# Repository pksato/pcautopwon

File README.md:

Small circuit using 555 timer to poweron a computer without option on BIOS to manage poweron behavior, in case of power loss. 
  
Its have three connection:  
5VSB to power circuit direct from PSU.  
5V to detect if main PSU is on.  
Connection to main board power on switch header.  
          
The 555 is configured as astable oscillator, generating a sort ~1s low pulse every ~10s. This pulse lit the optocoupler led and close the transistor, simulating push of the power button. When power is on (presence of 5V), transistor Q1 saturate, pulling down reset pin of 555, and avoiding the optocoupler led to lit. On reset condition, output pin of 555 goes do low. The circuit are build on top of PCB (as SMT), to easy fix the board inside the PC case.
  
EagleCad files and PNG images.
  
OBS.:
The mainboard where this circuit is used don't have option on BIOS to manage power state when mains AC return. And power on when power switch is released. Also, have a delay after mains applied and able to press power button.

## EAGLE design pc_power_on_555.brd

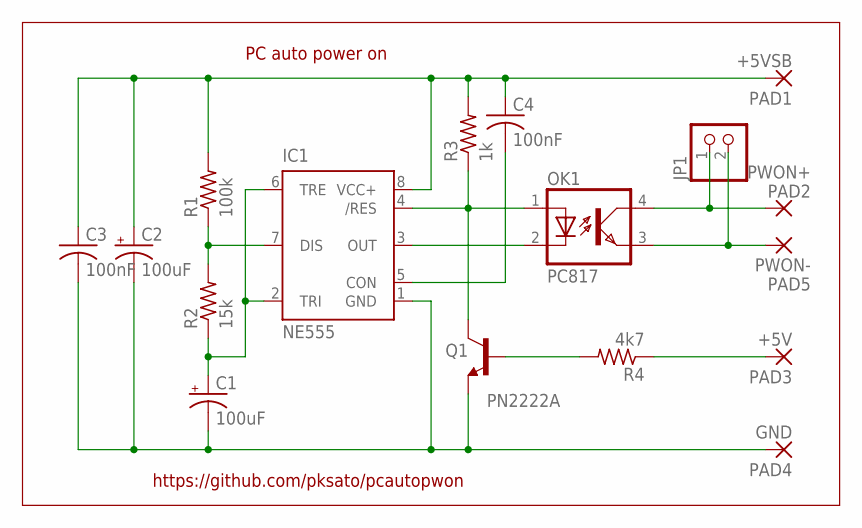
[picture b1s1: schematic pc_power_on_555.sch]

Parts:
C1, C2: 100uF; E2,5-7
C3, C4: 100nF; C025-030X050
IC1: NE555; DIL-08
JP1: PINHD-1X2; 1X02
OK1: PC817; DIL04
PAD1: +5VSB; 1,6/0,8
PAD2: PWON+; 1,6/0,8
PAD3: +5V; 1,6/0,8
PAD4: GND; 1,6/0,8
PAD5: PWON-; 1,6/0,8
Q1: PN2222A; TO92-EBC
R1: 100k; 0207/10
R2: 15k; 0207/10
R3: 1k; 0207/10
R4: 4k7; 0207/10

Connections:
unnamed: C1.+, IC1.2 (TRI), IC1.6 (TRE), R2.1
unnamed: IC1.7 (DIS), R1.1, R2.2
unnamed: IC1.3 (OUT), OK1.2 (C)
unnamed: C2.+, C3.1, C4.1, IC1.8 (VCC+), PAD1.1, R1.2, R3.2
unnamed: IC1.4 (/RES), OK1.1 (A), Q1.C, R3.1
unnamed: C1.-, C2.-, C3.2, IC1.1 (GND), PAD4.1, Q1.E
unnamed: JP1.2, OK1.3 (EMIT), PAD5.1
unnamed: JP1.1, OK1.4 (COL), PAD2.1
unnamed: Q1.B, R4.2
unnamed: PAD3.1, R4.1
unnamed: C4.2, IC1.5 (CON)

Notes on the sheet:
PC auto power on
https://github.com/pksato/pcautopwon

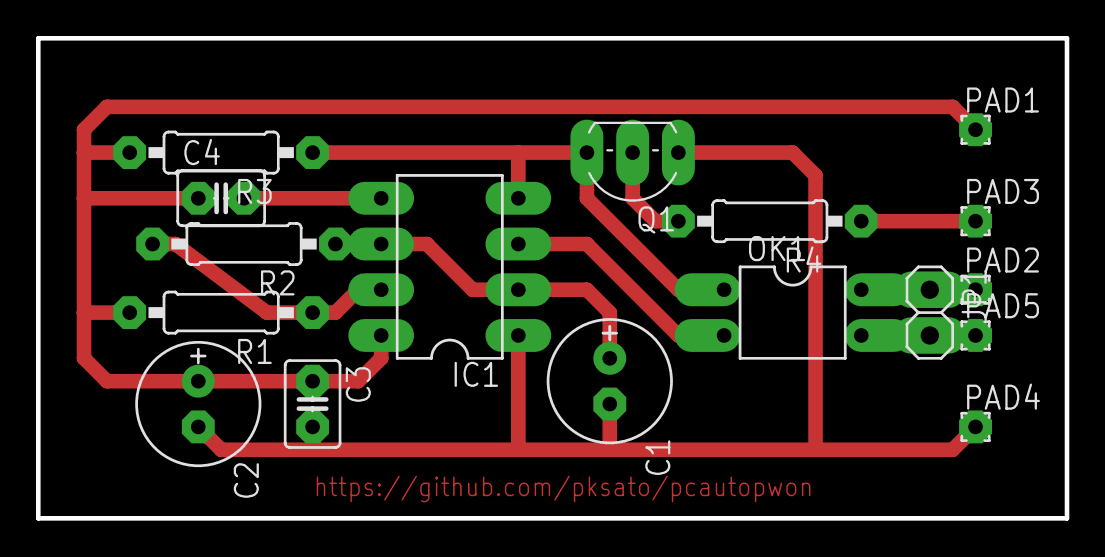
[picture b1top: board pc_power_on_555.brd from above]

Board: 2 copper layers, 57.1 x 26.7 mm, 17 parts (0 on the bottom side), 11 nets.
